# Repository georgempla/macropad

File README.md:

# George's Hackpad
After many hours of work I finally put everything together in what I hope is a functional hackpad. (A better picture will be added once everything is assembled)

### Inspiration
I recently learned about the blueprint program and decided it was the perfect way to gain some experience actually building stuff.

### Challenges
This was the first PCB I have ever designed (which is probably obvious from the wiring). Getting the software to work and learning the fundamental aspects of PCB design was challenging but thankfully my previous knowledge helped me overcome any problems.

### Firmware
After reading a lot of documentation this is what I came up with. Now obviously I can't test the code since I don't have anything similar so as soon as everything is assembled I will test, bug fix and upload the new code with any corrections that were made.

BOM: 
- 6x Cherry MX Switches
- 1x SK6812 MINI LED
- 1x XIAO RP2040
- 6x Blank DSA Keycaps
- 1x 3.3V I2C 0.91 Inch OLED Display

Others:
- Top Case.stl 
- Bottom Case.stl
- 4x 3D Printed Cylinders

Schematic            |  PCB         |   Case
:-------------------------:|:-------------------------:|:-------------------------:|
    |    |

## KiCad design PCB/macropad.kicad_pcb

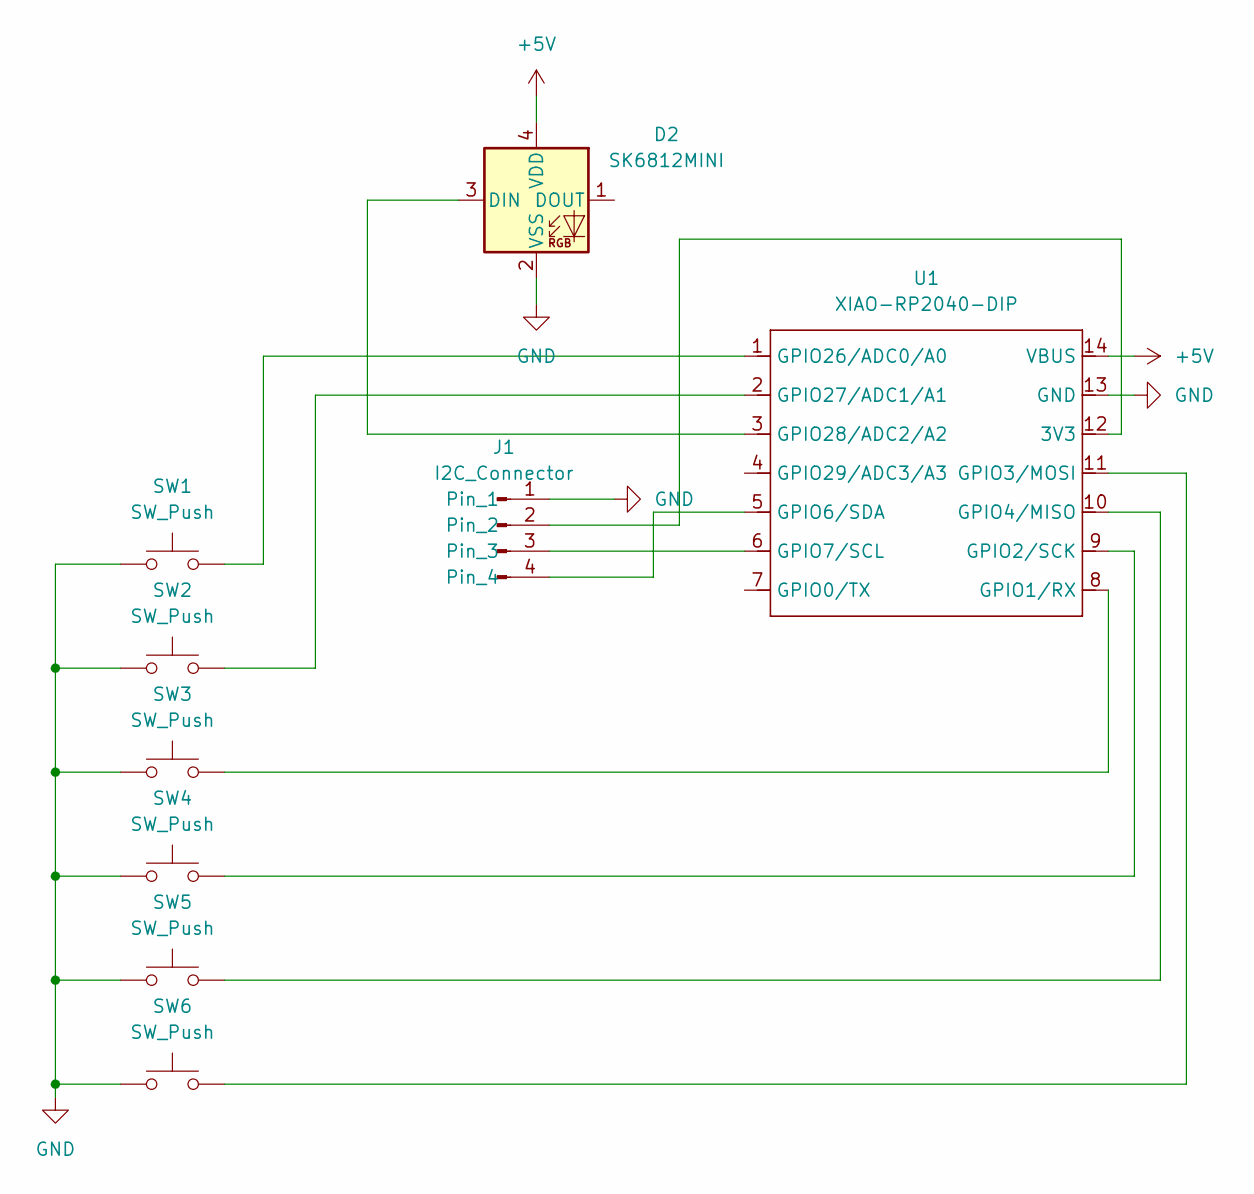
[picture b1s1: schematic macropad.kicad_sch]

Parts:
D2: SK6812MINI; LED_SK6812MINI_PLCC4_3.5x3.5mm_P1.75mm
J1: I2C_Connector; SSD1306-0.91-OLED-4pin-128x32
SW1, SW2, SW3, SW4, SW5, SW6: SW_Push; SW_Cherry_MX_1.00u_PCB
U1: XIAO-RP2040-DIP

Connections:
+5V: D2.4 (VDD), U1.14 (VBUS)
GND: D2.2 (VSS), J1.1, SW1.1, SW2.1, SW3.1, SW4.1, SW5.1, SW6.1, U1.13 (GND)
unnamed: D2.3 (DIN), U1.3 (GPIO28/ADC2/A2)
unnamed: J1.2, U1.12 (3V3)
unnamed: J1.3, U1.6 (GPIO7/SCL)
unnamed: J1.4, U1.5 (GPIO6/SDA)
unnamed: SW3.2, U1.8 (GPIO1/RX)
unnamed: SW4.2, U1.9 (GPIO2/SCK)
unnamed: SW6.2, U1.11 (GPIO3/MOSI)
unnamed: SW5.2, U1.10 (GPIO4/MISO)
unnamed: SW1.2, U1.1 (GPIO26/ADC0/A0)
unnamed: SW2.2, U1.2 (GPIO27/ADC1/A1)

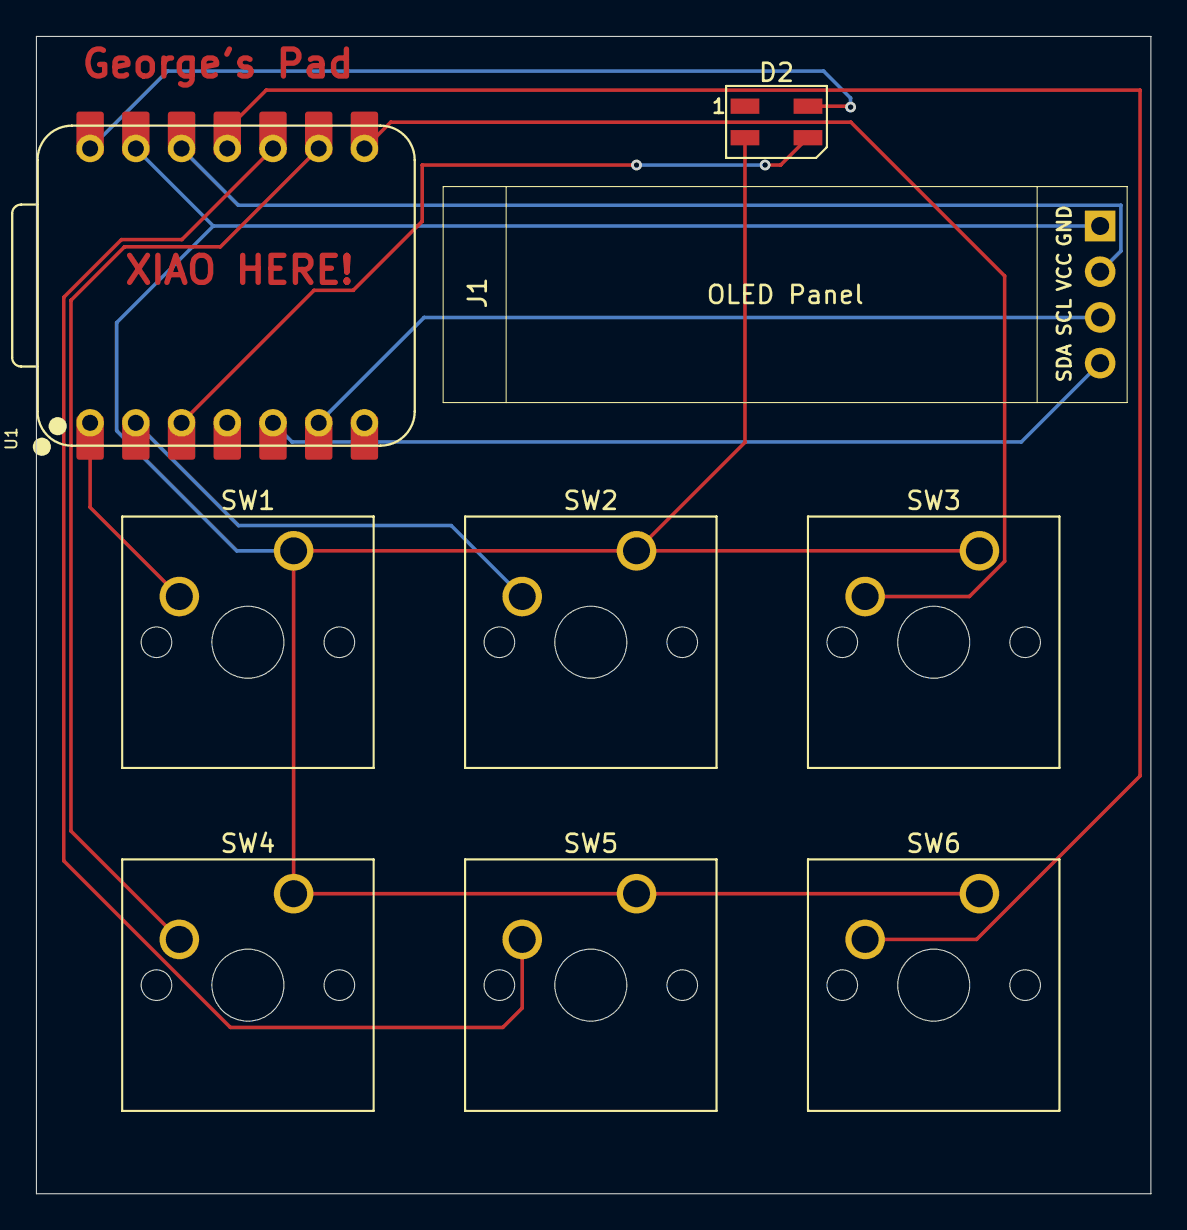
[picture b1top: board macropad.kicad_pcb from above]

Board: 2 copper layers, 61.9 x 64.3 mm, 9 parts (0 on the bottom side), 12 nets.

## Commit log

2026-01-05 Initial Upload
2026-01-06 add .step and adjust case
2026-01-06 image and schematic updates
2026-01-06 uploaded .step 3d models
